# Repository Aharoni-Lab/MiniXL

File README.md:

# Miniscope extra Large FOV (MiniXL) 

**[[Miniscope V4 Wiki](https://github.com/Aharoni-Lab/Miniscope-v4/wiki)] [[Miniscope DAQ Software Wiki](https://github.com/Aharoni-Lab/Miniscope-DAQ-QT-Software/wiki)] [[Miniscope DAQ Firmware Wiki](https://github.com/Aharoni-Lab/Miniscope-DAQ-Cypress-firmware/wiki)] [[Miniscope Wire-Free DAQ Wiki](https://github.com/Aharoni-Lab/Miniscope-Wire-Free-DAQ/wiki)] [[MiniLFOV-Light Wiki](https://github.com/Aharoni-Lab/Miniscope-LFOV/wiki)][[2021 Virtual Miniscope Workshop Recording](https://sites.google.com/metacell.us/miniscope-workshop-2021)]**

This is the repository for the second version of MiniLFOV, called MiniXL, which is able to image the neuronal acitivity in freely moving mice with a field of view larger than 3mm and single cell resolution.
Large field-of-view miniature microscope for freely moving mice and bigger animals. 

<p dir="auto"><strong>All information, guides, and tutorials can be found on the <a href="https://github.com/Aharoni-Lab/MiniLFOV-Light?tab=readme-ov-file">MiniLFOV-Light Wiki Page</a>.</strong></p>
<p dir="auto"><strong>Make sure to click Watch and Star in the upper right corner of this page to get updates on new features and releases.</strong></p>
<p align="center" dir="auto">
<p dir="auto">The MiniXL is designed to extend the capabilities of the UCLA Miniscope for imaging in freely moving mice, and imaging to larger rodents and non-human primates. This system is capable of multiple imaging configurations, including deep brain imaging using implanted optical probes and cortical imaging through cranial windows. Some feature highlights are listed below.</p>
<ul dir="auto">
<li>3.5 mm field of view</li>
<li>~3 µm resolution</li>
<li>1.9 mm working distance</li>
<li>+/-200 µm electronic focal adjustment</li>
<li>Modular optics</li>
<li>Achromatic optics</li>
<li>3.5 grams</li>
<li>30 mm tall</li>
<li>Absolute head orientation sensor</li>
<li>Requires ~1/2th the excitation power of previous systems</li>
<li>No more soldering!</li>
<li>Still uses only a single coaxial cable (down to 0.3mm in diameter) for power, communication, and data.</li>
<li>New DAQ software</li>
</ul>

## How to use with the Miniscope DAQ Software
The MiniXL needs an updated videoDevices.json file which holds the configuration data for different modes the MiniLFOV-XL is able to run in. This file can be found in the Miniscope_DAQ_Software_Configurations folder in this repository and should replace the same named fiel in the deviceConfig folder of the Miniscope Software.

We have also included an example user configuration file that will run the MiniLFOV-XL in its 2x binning and summing mode.

## How to cite
A paper discussing the MiniLFOV and Miniscope Wire-Free DAQ can be found [here](https://www.science.org/doi/10.1126/sciadv.adg3918). Please use the following citation information.

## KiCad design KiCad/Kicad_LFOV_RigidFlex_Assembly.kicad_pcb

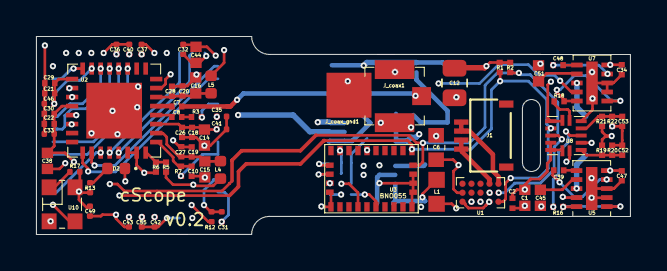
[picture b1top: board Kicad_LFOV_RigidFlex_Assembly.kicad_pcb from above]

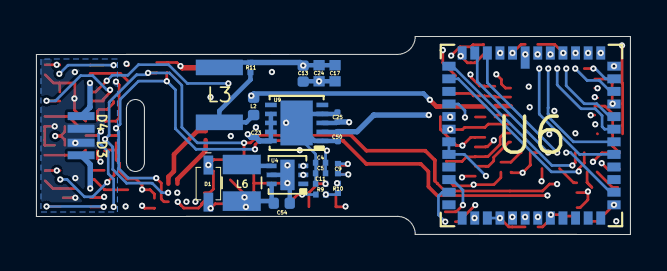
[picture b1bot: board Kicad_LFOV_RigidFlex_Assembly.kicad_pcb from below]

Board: 4 copper layers, 33.0 x 11.0 mm, 95 parts (23 on the bottom side), 56 nets.

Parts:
C1, C14, C15, C45, C51: GRM155R60J475ME87D; C_0402_1005Metric_L
C2, C5, C7, C9, C11, C18, C19, C20, C21, C22, C52, C53: GRM033R61A104ME15D; C_0201_0603Metric_L
C4, C26, C27, C28, C29, C30: GRM033R71A103KA01D; C_0201_0603Metric_L
C6: GRJ188R72A104KE11D; C_0603_1608Metric_L
C8: GRM033R61C473KE84D; C_0201_0603Metric_L
C10: GRM033R61A105ME15D; R_0201_0603Metric_ERJ_L
C12: GRM21BR61A476ME15L; C_0805_2012Metric_L
C13, C38: 10uF; C_0402_1005Metric_L
C16, C17, C24, C44: GRM155R60J106ME15D; C_0402_1005Metric_L
C23, C25, C31, C32, C33, C50: 1uF; C_0201_0603Metric_L
C34, C39, C47, C48: GRM033R61A225ME47D; C_0201_0603Metric_L
C35, C36, C37, C40, C41, C42, C43, C46, C55: 0.1uF; C_0201_0603Metric_L
C49: 10nF; C_0201_0603Metric_L
C54: 22uF; C_0402_1005Metric_L
D1: BAS316-TP; SOD_323_250X125X110L30X32L
D2: LED 0402; LED_0402_1005Metric
D3, D4: LXZ1-PB01; LED_LXZ1_PR01_L
J1: FH19C-4S-0.5SH(10)
J_coax1: U.FL-R-SMT-1(10); Coax_Conn_U.FL
J_coax_gnd1: Conn_01x01; Conn_1x1_100x100_Pad
L1: LQM18PN3R3MGHD; L_0603_1608Metric_L
L2, L4, L5: BLM15HD102SN1D; L_0402_1005Metric
L3: ADL3225V-470MT-TL000; L_1210_3225Metric_L
L6: LQM2HPN1R0MG0; L_1008_2520Metric_L
R1, R2: ERJ-1GNF3321C; R_0201_0603Metric_ERJ_L
R3: ERJ-1GNF49R9C; R_0201_0603Metric_ERJ_L
R5, R7, R9, R10, R16: ERJ-1GNF1022C; R_0201_0603Metric_ERJ_L
R6: ERJ-1GNF1003C; R_0201_0603Metric_ERJ_L
R11: ERJ-1GNF1801C; R_0201_0603Metric_ERJ_L
R12: 1k; R_0201_0603Metric_ERJ_L
R13: 500; R_0201_0603Metric_ERJ_L
R17: DNL; R_0201_0603Metric_ERJ_L
R18: ERJ-1GEF1022C; R_0201_0603Metric_ERJ_L
R19, R21: ERJ-1GNJ622C; R_0201_0603Metric_ERJ_L
R20, R22: ERJ-1GNF3741C; R_0201_0603Metric_ERJ_L
U1: MAX14574EWL+; BGA_15_NP50_3X5_155X255X69B31N
U2: DS90UB913ATRTVTQ1; QFN_33_P50_500X500X80L40X24T310L
U3: BNO055; LGA28R50P4X10_380X520X100
U4: SC189ZULTRT; SON_7P50_200X200X57L35X24T170X80N
U5, U7: LTC3218; SON_11_P50_300X200X80L40X25T239X64L
U6: MT9P031I12STM-DP; iLCC48P70_1000X1000X135L80X40N
U8: TPL0102-100RUCR; QFN_14_P40_200X200X40L40X20L
U9: NCV8154MW180280TBG; DFN10_3x3_11P50_300X300X100L40X24T250X180N
U10: SG-210STF 66.6667ML3; OSC_CC250X200X80L70X75L

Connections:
+3V3: C1.1, C2.1, C4.1, C5.1, C9.2, C12.1, C23.1, C34.1, C47.1, C54.1, L1.1, L6.2, R1.2, R2.2, R9.1, R10.1, R19.1, R21.1, U1.A3, U1.B2, U3.3, U3.28, U4.6, U5.10, U7.10, U8.14, U9.7, U9.8, U9.9, U9.10
+5V: C13.1, C17.1, C24.1, L3.2, R11.1, U4.2, U4.3
/CAP: C11.2, U3.9
/ENT: U2.15, U5.4, U7.4
/EWL1: J1.1, J1.2, U1.C2
/EWL2: J1.3, J1.4, U1.C1
/EXTCLK: U6.31, U10.3
/RESET_BAR: C31.1, R12.2, U6.16
/Va: C52.1, R19.2, R20.1, U8.1
/Vb: C53.1, R21.2, R22.1, U8.4
/_Wa: R16.1, U8.3
/_Wb: R18.1, U8.6
CLK_OUT: U2.3, U6.32
DIN0: U2.19, U6.35
DIN1: U2.20, U6.36
DIN2: U2.21, U6.37
DIN3: U2.22, U6.38
DIN4: U2.23, U6.40
DIN5: U2.24, U6.41
DIN6: U2.26, U6.42
DIN7: U2.27, U6.43
DIN8: U2.29, U6.44
DIN9: U2.30, U6.45
DOUT_P: C7.1, J_coax1.2, L2.1
FV: U2.2, U6.7
GND: C1.2, C2.2, C4.2, C5.2, C6.2, C9.1, C10.2, C11.1, C12.2, C13.2, C14.2, C15.2, C16.2, C17.2, C18.2, C19.2, C20.2, C21.2, C22.2, C23.2, C24.2, C25.2, C26.2, C27.2, C28.2, C29.2, C30.2, C31.2, C32.2, C33.2, C34.2, C35.2, C36.2, C37.2, C38.2, C40.2, C41.2, C42.2, C43.2, C44.2, C45.2, C46.2, C47.2, C49.2, C50.2, C51.2, C52.2, C53.2, C54.2, C55.2, D2.1, D3.C, D4.C, J_coax1.1, J_coax_gnd1.1, R3.1, R6.2, R20.2, R22.2, U1.A2, U1.A5, U2.6, U2.7, U2.33, U3.2, U3.5, U3.6, U3.15, U3.16, U3.17, U3.18, U3.25, U4.5, U4.7, U5.7, U5.8, U5.11, U6.2, U6.3, U6.6, U6.10, U6.17, U6.20, U6.21, U6.22, U6.26, U6.46, U7.7, U7.8, U7.11, U8.2, U8.5, U8.7, U8.8, U8.11, U8.12, U8.13, U9.1, U9.4, U9.11, U10.2
I2C_SCL: R2.1, U1.B1, U2.4, U3.19, U6.4, U8.10
I2C_SDA: R1.1, U1.A1, U2.5, U3.20, U6.5, U8.9
LV: U2.1, U6.8
MODE: R5.2, R6.1, U2.8
unnamed: C6.1, D1.C, U1.B5
unnamed: C7.2, U2.13
unnamed: C8.1, R3.2
unnamed: C8.2, U2.12
unnamed: C39.1, U5.9
unnamed: C39.2, U5.1
unnamed: C45.1, U5.2
unnamed: C48.1, U7.9
unnamed: C48.2, U7.1
unnamed: C51.1, U7.2
unnamed: D1.A, L1.2, U1.A4
unnamed: D2.2, R13.1
unnamed: D3.A, U5.3
unnamed: D4.A, U7.3
unnamed: L2.2, L3.1, R11.2
unnamed: L6.1, U4.4
unnamed: R9.2, U3.11
unnamed: R10.2, U3.4
unnamed: R16.2, U5.5, U5.6
unnamed: R17.2, U10.1
unnamed: R18.2, U7.5, U7.6
PDB: C10.1, R7.2, U2.9
VDDCML: C16.1, C20.1, C28.1, L5.1, U2.14
VDDD: C14.1, C18.1, C22.1, C26.1, C30.1, C33.1, C36.1, C38.1, C41.1, C50.1, L4.2, L5.2, R5.1, U2.11, U2.28, U6.12, U6.47, U9.2
VDDIO: C21.1, C25.1, C29.1, C32.1, C35.1, C37.1, C40.1, C42.1, C43.1, C44.1, C46.1, C49.1, C55.1, R7.1, R12.1, R13.2, R17.1, U2.25, U6.1, U6.11, U6.13, U6.14, U6.23, U6.24, U6.25, U6.39, U6.48, U9.3, U10.4
VDDPLL: C15.1, C19.1, C27.1, L4.1, U2.10

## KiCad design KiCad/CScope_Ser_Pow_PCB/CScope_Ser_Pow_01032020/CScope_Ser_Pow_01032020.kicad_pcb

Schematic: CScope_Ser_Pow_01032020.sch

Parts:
C1: C_Small; C_0805_2012Metric_L
C4, C5, C26: GRM155R60J106ME15D; C_0402_1005Metric_L
C6, C7, C8, C11: GRM033R61A105ME15D; C_0201_0603Metric_L
C9, C19, C21, C24, C27, C29: GRM033R61A104ME15D; C_0201_0603Metric_L
C10: GRM033R61C473KE84D; C_0201_0603Metric_L
C18, C23: GRM155R60J475ME87D; C_0402_1005Metric_L
C20, C22, C25, C28, C30: GRM033R71A103KA01D; C_0201_0603Metric_L
J16: Conn_01x20_Female; B2B_Flex_20_Dual_Row_38milx24mil_Pad_20mil
J_3V3: Conn_01x01; Conn_1x1_700_Circular_Pad
J_coax1: U_FL-R-SMT_10_; Coax_Conn_U.FL; MPN U.FL-R-SMT(10); Digi-Key_PN H9161CT-ND
J_coax_gnd1: Conn_01x01; Conn_1x1_100x100_Pad
J_extra1, J_extra2: Conn_01x05; B2B_Flex_05_Dual_Row_38milx24mil_Pad_20mil
J_extra3: Conn_01x05; B2B_Flex_05_Dual_Row_38milx24mil_Pad_20mil_copy
L1: ADL3225V-470MT-TL000; L_1210_3225Metric_L
L2, L4, L5: BLM15HD102SN1D; L_0402_1005Metric
R1: MMBT3904LP-7B; R_0201_0603Metric_ERJ_L
R2: ERJ-1GEF49R9C; R_0201_0603Metric_ERJ_L
R3, R4: ERJ-1GEF1022C; R_0201_0603Metric_ERJ_L
R5, R6: ERJ-1GEF3321C; R_0201_0603Metric_ERJ_L
R7: ERJ-1GEF1003C; R_0201_0603Metric_ERJ_L
U1: DS90UB913Q-Q1; QFN_33_P50_500X500X80L40X24T310L
U3: TLV7103318DSER; SON_6_P50_150X150X80L50X25L

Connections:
+3V3: C1.1, C6.1, J_3V3.1, J_extra1.4, J_extra2.5, J_extra3.5, R5.1, R6.1, U3.6 (OUT1)
+5V: C4.1, C5.1, C7.1, J16.18, J_extra2.4, L1.2, R1.1, U3.1 (EN1), U3.2 (IN), U3.3 (EN2)
/ENT1: J_extra3.1, U1.16 (GPO[1])
/ENT2: U1.15 (GPO[0])
CLK_OUT: J16.7, J_extra1.3, U1.3 (PCLK)
DIN0: J16.3, U1.19 (DIN[0])
DIN1: J16.5, U1.20 (DIN[1])
DIN2: J16.4, U1.21 (DIN[2])
DIN3: J16.6, U1.22 (DIN[3])
DIN4: J16.8, U1.23 (DIN[4])
DIN5: J16.9, U1.24 (DIN[5])
DIN6: J16.11, U1.26 (DIN[6])
DIN7: J16.10, U1.27 (DIN[7])
DIN8: J16.12, U1.29 (DIN[8])
DIN9: J16.13, U1.30 (DIN[9])
DIN10: J_extra1.1, U1.31 (DIN[10])
DIN11: J_extra1.2, U1.32 (DIN[11])
DOUT_P: C9.1, J_coax1.2, L2.1
FV: J16.14, U1.2 (VSYNC)
GND: C1.2, C4.2, C5.2, C6.2, C7.2, C8.2, C11.2, C18.2, C19.2, C20.2, C21.2, C22.2, C23.2, C24.2, C25.2, C26.2, C27.2, C28.2, C29.2, C30.2, J16.1, J16.20, J_coax1.1, J_coax_gnd1.1, J_extra1.5, J_extra2.3, J_extra3.4, R2.1, R7.2, U1.6 (ID[x]), U1.7 (RES), U1.33 (VSS), U3.4 (GND)
I2C_SCL: J16.17, J_extra2.1, J_extra3.2, R5.2, U1.4 (SCL)
I2C_SDA: J16.16, J_extra2.2, J_extra3.3, R6.2, U1.5 (SDA)
LV: J16.15, U1.1 (HSYNC)
MODE: R3.2, R7.1, U1.8 (MODE)
unnamed: C9.2, U1.13 (DOUT+)
unnamed: C10.1, R2.2
unnamed: C10.2, U1.12 (DOUT-)
unnamed: L1.1, L2.2, R1.2
PDB: C11.1, R4.2, U1.9 (PDB)
VDDCML: C26.1, C27.1, C28.1, L5.1, U1.14 (VDDCML)
VDDD: C8.1, C18.1, C19.1, C20.1, C29.1, C30.1, J16.2, L4.2, L5.2, R3.1, U1.11 (VDDT), U1.28 (VDDD), U3.5 (OUT2)
VDDIO: C21.1, C22.1, J16.19, R4.1, U1.25 (VDDIO)
VDDPLL: C23.1, C24.1, C25.1, L4.1, U1.10 (VDDPLL)

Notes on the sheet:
Can be swapped out with the DS90UB913 variant
Open as said in the datasheet ds90ub933-q1.pdf Page 4

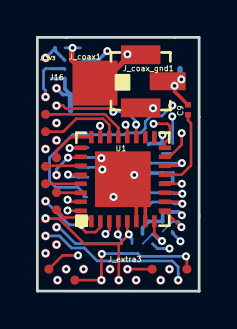
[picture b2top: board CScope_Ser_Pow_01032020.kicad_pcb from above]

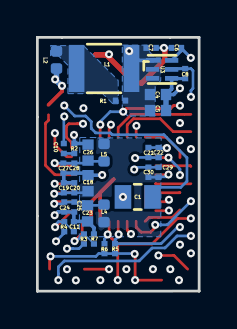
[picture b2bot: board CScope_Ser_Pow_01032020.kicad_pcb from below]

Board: 6 copper layers, 9.0 x 14.1 mm, 42 parts (33 on the bottom side), 32 nets.

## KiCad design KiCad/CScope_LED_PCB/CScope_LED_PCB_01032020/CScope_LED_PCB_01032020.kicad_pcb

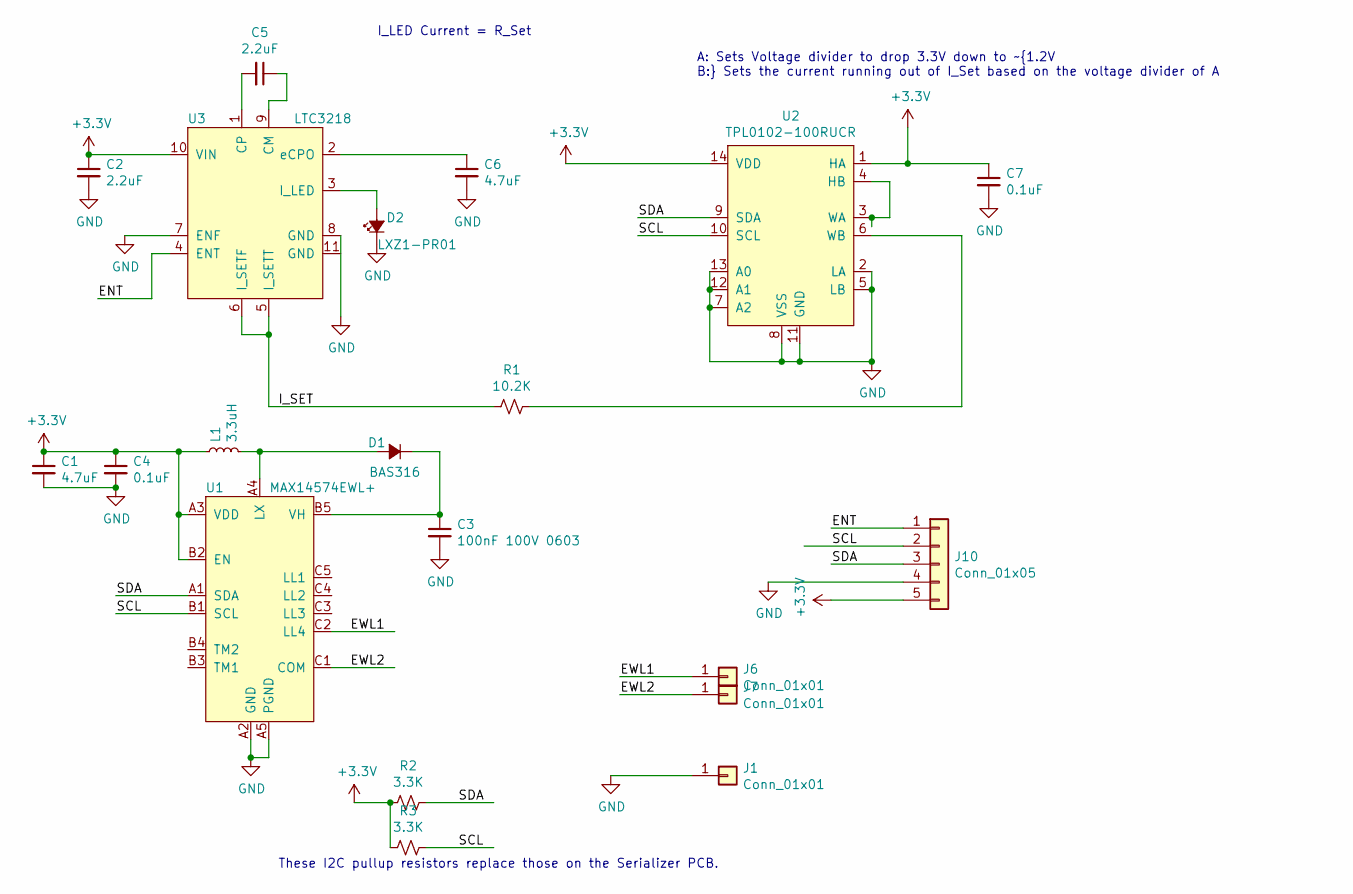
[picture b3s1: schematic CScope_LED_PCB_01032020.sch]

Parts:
C1, C6: GRM155R60J475ME87D; C_0402_1005Metric_L
C2, C5: GRM033R61A225ME47D; C_0201_0603Metric_L
C3: 100nF 100V 0603; C_0603_1608Metric_L
C4, C7: GRM033R61A104ME15D; C_0201_0603Metric_L
D1: BAS316; SOD_323_250X125X110L30X32L
D2: LXZ1-PR01; LED_LXZ1_PR01_L
J1, J6, J7: Conn_01x01; Conn_1x1_250x750_Pad
J10: Conn_01x05; B2B_Flex_05_Dual_Row_38milx24mil_Pad_20mil_copy
L1: LQM18PN3R3MGHD; L_0603_1608Metric_L
R1, R2, R3: ERJ-1GEF1022C; R_0201_0603Metric_ERJ_L
U1: MAX14574EWL+; BGA_15_NP50_3X5_155X255X69B31N
U2: TPL0102-100RUCR; QFN_14_P40_200X200X40L40X20L
U3: LTC3218; SON_11_P50_300X200X80L40X25T239X64L

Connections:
+3V3: C1.1, C2.1, C4.1, C7.1, J10.5, L1.1, R2.2, R3.2, U1.A3 (VDD), U1.B2 (EN), U2.1 (HA), U2.14 (VDD), U3.10 (VIN)
/ENT: J10.1, U3.4 (ENT)
/EWL1: J6.1, U1.C2 (LL4)
/EWL2: J7.1, U1.C1 (COM)
/I_SET: R1.2, U3.5 (I_SETT), U3.6 (I_SETF)
/SCL: J10.2, R3.1, U1.B1 (SCL), U2.10 (SCL)
/SDA: J10.3, R2.1, U1.A1 (SDA), U2.9 (SDA)
GND: C1.2, C2.2, C3.2, C4.2, C6.2, C7.2, D2.C, J1.1, J10.4, U1.A2 (GND), U1.A5 (PGND), U2.2 (LA), U2.5 (LB), U2.7 (A2), U2.8 (VSS), U2.11 (GND), U2.12 (A1), U2.13 (A0), U3.7 (ENF), U3.8 (GND)
unnamed: C3.1, D1.C, U1.B5 (VH)
unnamed: C5.1, U3.9 (CM)
unnamed: C5.2, U3.1 (CP)
unnamed: C6.1, U3.2 (eCPO)
unnamed: D1.A, L1.2, U1.A4 (LX)
unnamed: D2.A, U3.3 (I_LED)
unnamed: R1.1, U2.6 (WB)
unnamed: U2.3 (WA), U2.4 (HB)

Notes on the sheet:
I_LED Current = R_Set
A: Sets Voltage divider to drop 3.3V down to ~1.2V B: Sets the current running out of I_Set based on the voltage divider of A
These I2C pullup resistors replace those on the Serializer PCB.

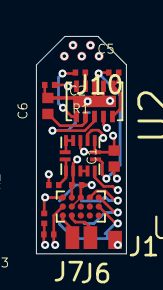
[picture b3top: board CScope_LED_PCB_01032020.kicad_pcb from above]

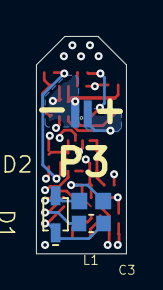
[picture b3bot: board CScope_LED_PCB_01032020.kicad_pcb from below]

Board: 6 copper layers, 5.0 x 12.1 mm, 20 parts (4 on the bottom side), 16 nets.

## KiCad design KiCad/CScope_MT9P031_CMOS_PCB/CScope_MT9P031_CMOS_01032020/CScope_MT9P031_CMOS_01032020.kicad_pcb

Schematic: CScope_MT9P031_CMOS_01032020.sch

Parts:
C1, C3, C5, C7, C13, C14, C16: 10uF; C_0402_1005Metric_L
C2, C4, C6, C8, C11, C15, C17: .1uF; C_0402_1005Metric_L
C12: .01uF; C_0402_1005Metric_L
C18: 10nF; C_0402_1005Metric_L
C19: 1uF; C_0402_1005Metric_L
D1: LED_Small_ALT; LED_SC80X160X65L40L
J1: Conn_01x20; B2B_Flex_20_Dual_Row_38milx24mil_Pad_20mil
J2: Conn_01x05; B2B_Flex_05_Dual_Row_38milx24mil_Pad_20mil_copy
J3: Conn_01x01; Conn_1x1_700_Circular_Pad
R3: DNL; R_0402_1005Metric_ERJ_L
R4: 1K; R_0402_1005Metric_ERJ_L
R5: 500; R_0402_1005Metric_ERJ_L
U1: TPS79328-EP; SOT-23-5
U2: SiT_2.5mmx2mm; OSC_CC250X200X80L70X75L
U3: MT9P031; iLCC48P70_1000X1000X135L80X40N

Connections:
+1V8: C14.1, C15.1, C16.1, C17.1, J1.2, U3.12, U3.47
+2V8: C1.1, C2.1, C3.1, C4.1, C5.1, C6.1, C7.1, C8.1, C13.1, C18.1, J1.19, R3.1, R4.1, U1.5 (OUT), U2.4 (VDD), U3.1, U3.11, U3.13, U3.14, U3.23, U3.24, U3.25, U3.39, U3.48
+3V3: J2.1, J3.1
+5V: C11.1, J1.18, R5.2, U1.1 (IN), U1.3 (EN)
/DOUT0: U3.33
/DOUT1: U3.34
/DOUT2: J1.3, U3.35
/DOUT3: J1.5, U3.36
/DOUT4: J1.4, U3.37
/DOUT5: J1.6, U3.38
/DOUT6: J1.8, U3.40
/DOUT7: J1.9, U3.41
/DOUT8: J1.11, U3.42
/DOUT9: J1.10, U3.43
/DOUT10: J1.12, U3.44
/DOUT11: J1.13, U3.45
/ENT: J2.5
/EXTCLK: U2.3 (OUT), U3.31
/FV: J1.14, U3.7
/LV: J1.15, U3.8
/PIXCLK: J1.7, U3.32
/RESET_BAR: C19.1, R4.2, U3.16
/SCLK: J1.17, J2.4, U3.4
/SDATA: J1.16, J2.3, U3.5
/STROBE: U3.9
/TRIGGER: U3.15
GND: C1.2, C2.2, C3.2, C4.2, C5.2, C6.2, C7.2, C8.2, C11.2, C12.2, C13.2, C14.2, C15.2, C16.2, C17.2, C18.2, C19.2, D1.1 (K), J1.1, J1.20, J2.2, U1.2 (GND), U2.2 (GND), U3.2, U3.3, U3.6, U3.10, U3.17, U3.20, U3.21, U3.22, U3.26, U3.46
unnamed: C12.1, U1.4 (BP)
unnamed: D1.2 (A), R5.1
unnamed: R3.2, U2.1 (OE/nST/NC)

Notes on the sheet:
Sends 2.8V back to Ser Pow PCB for VCCIO

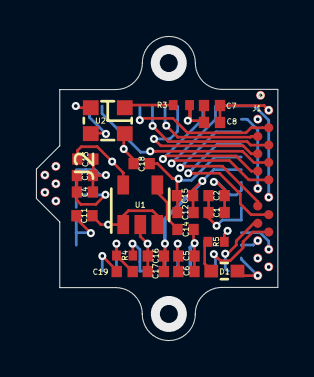
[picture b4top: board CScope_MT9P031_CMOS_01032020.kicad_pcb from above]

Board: 6 copper layers, 13.4 x 16.9 mm, 27 parts (1 on the bottom side), 25 nets.

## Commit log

2024-06-08 Create Zemax
2024-06-08 zemax files of MiniLFOV_XL
2024-06-08 Bodies and kicad
2024-07-12 images
